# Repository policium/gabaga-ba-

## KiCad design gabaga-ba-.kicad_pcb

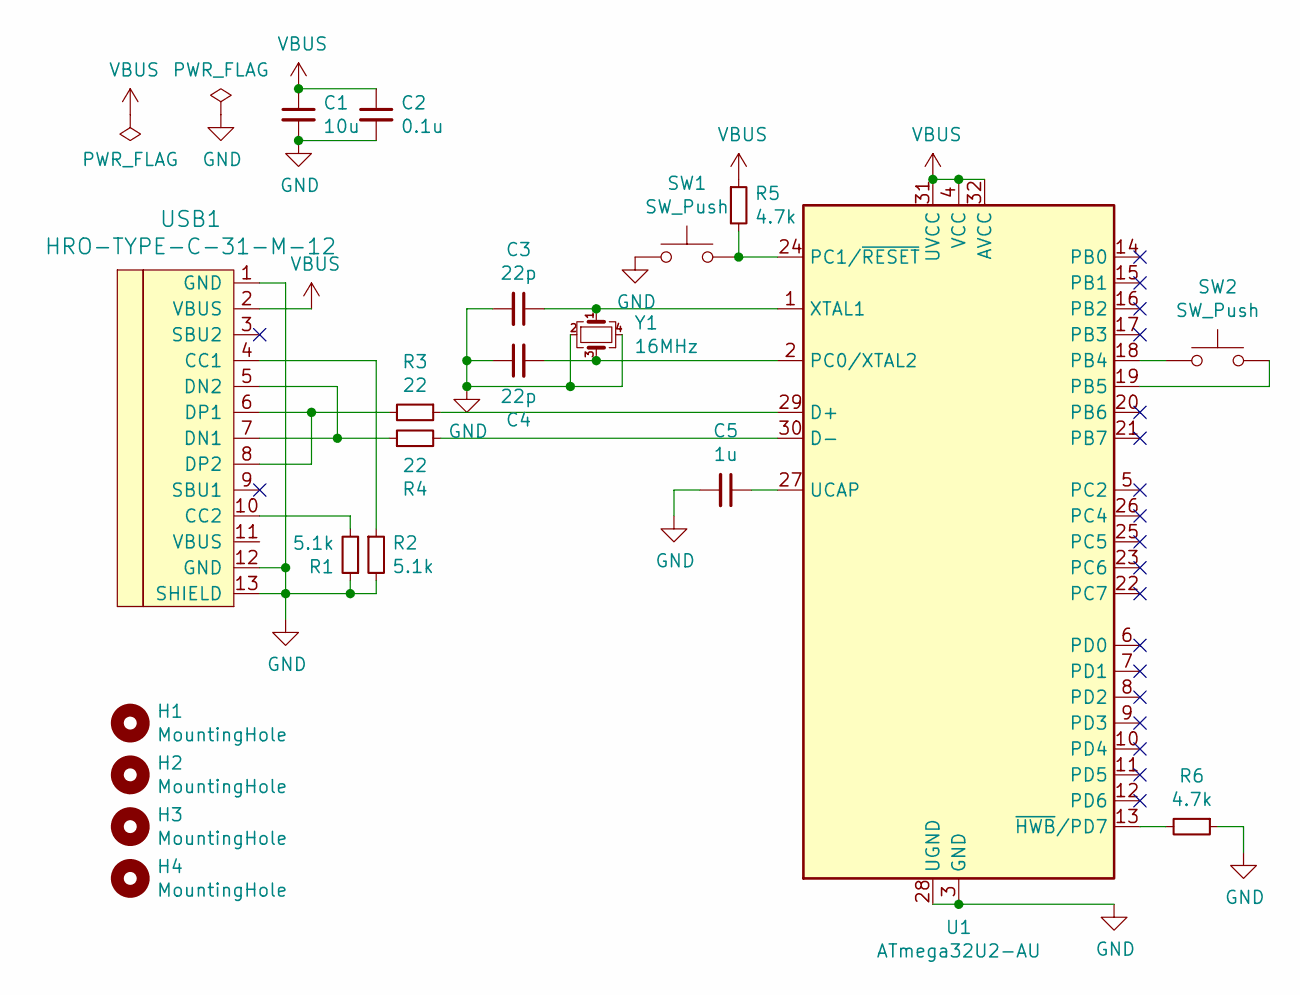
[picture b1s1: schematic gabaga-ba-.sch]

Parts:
C1: 10u; C_0805_2012Metric
C2: 0.1u; C_0805_2012Metric
C3, C4: 22p; C_0805_2012Metric
C5: 1u; C_0805_2012Metric
H1, H2, H3, H4: MountingHole; MountingHole_3.2mm_M3
R1, R2: 5.1k; R_0805_2012Metric
R3, R4: 22; R_0805_2012Metric
R5, R6: 4.7k; R_0805_2012Metric
SW1: SW_Push; SW_SPST_SKQG_WithStem
SW2: SW_Push; kailh_big_series
U1: ATmega32U2-AU; TQFP-32_7x7mm_P0.8mm
USB1: HRO-TYPE-C-31-M-12
Y1: 16MHz; Crystal_SMD_5032-4Pin_5.0x3.2mm

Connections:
GND: C1.2, C2.2, C3.2, C4.1, C5.2, R1.1, R2.2, R6.1, SW1.1, U1.3 (GND), U1.28 (UGND), USB1.1 (GND), USB1.12 (GND), USB1.13 (SHIELD), Y1.2, Y1.4
unnamed: C3.1, U1.1 (XTAL1), Y1.1
unnamed: C4.2, U1.2 (PC0/XTAL2), Y1.3
unnamed: C5.1, U1.27 (UCAP)
unnamed: R1.2, USB1.10 (CC2)
unnamed: R2.1, USB1.4 (CC1)
unnamed: R3.1, U1.29 (D+)
unnamed: R3.2, USB1.6 (DP1), USB1.8 (DP2)
unnamed: R4.1, USB1.5 (DN2), USB1.7 (DN1)
unnamed: R4.2, U1.30 (D-)
unnamed: R5.2, SW1.2, U1.24 (PC1/~RESET)
unnamed: R6.2, U1.13 (~HWB~/PD7)
unnamed: SW2.1, U1.18 (PB4)
unnamed: SW2.2, U1.19 (PB5)
VBUS: C1.1, C2.1, R5.1, U1.4 (VCC), U1.31 (UVCC), U1.32 (AVCC), USB1.2 (VBUS)

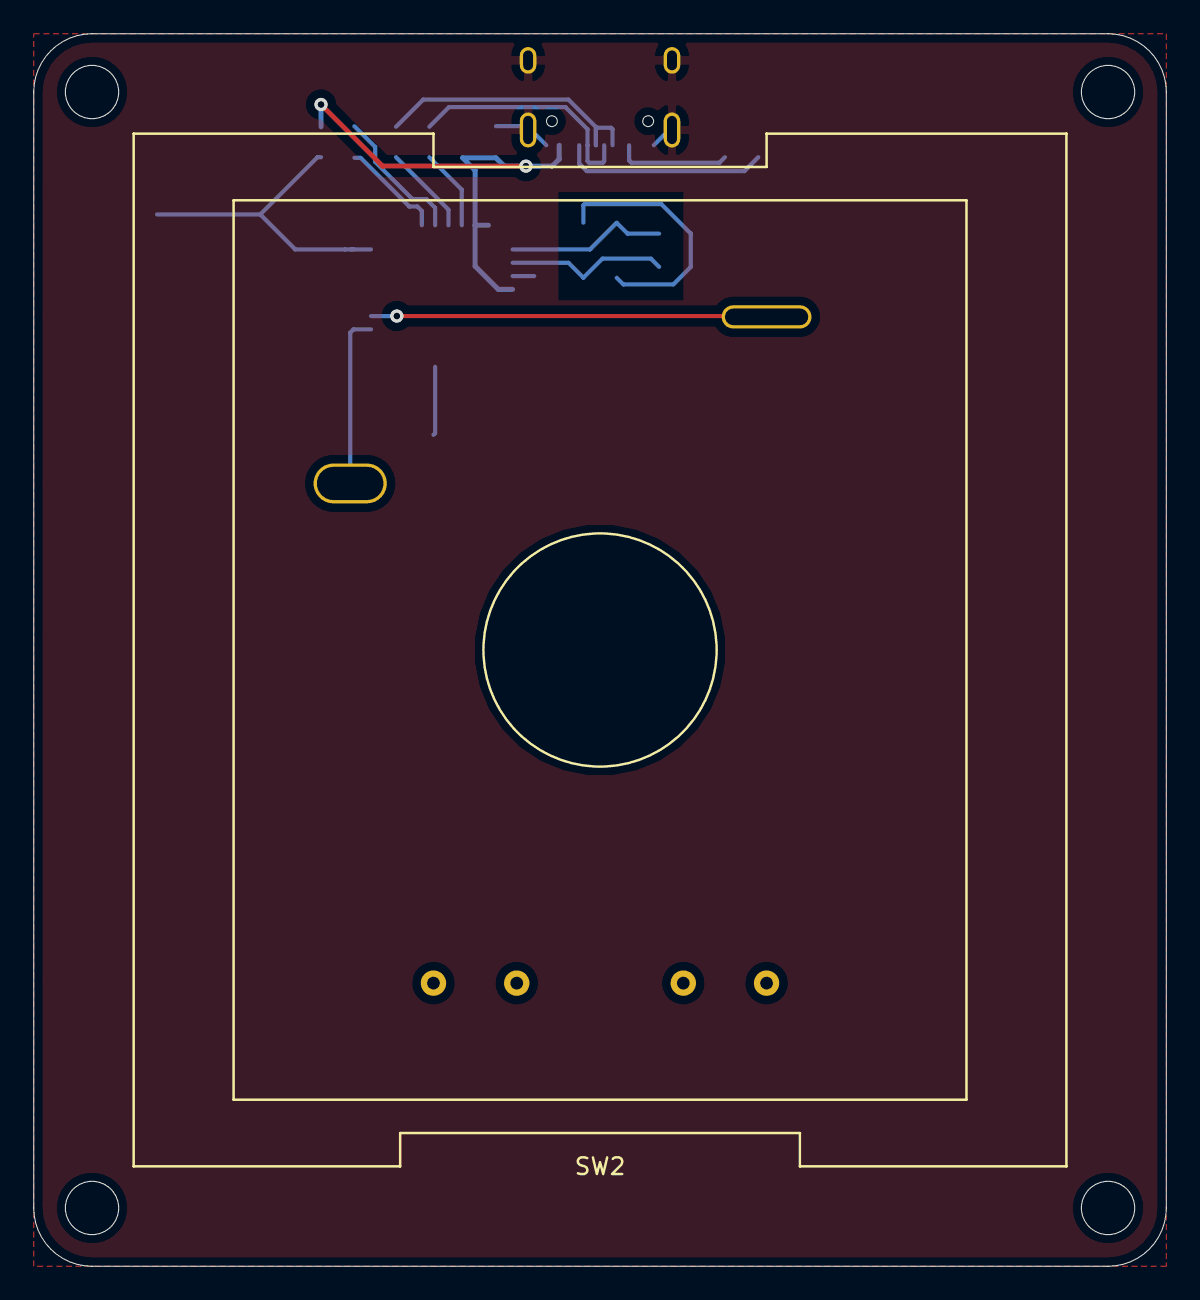
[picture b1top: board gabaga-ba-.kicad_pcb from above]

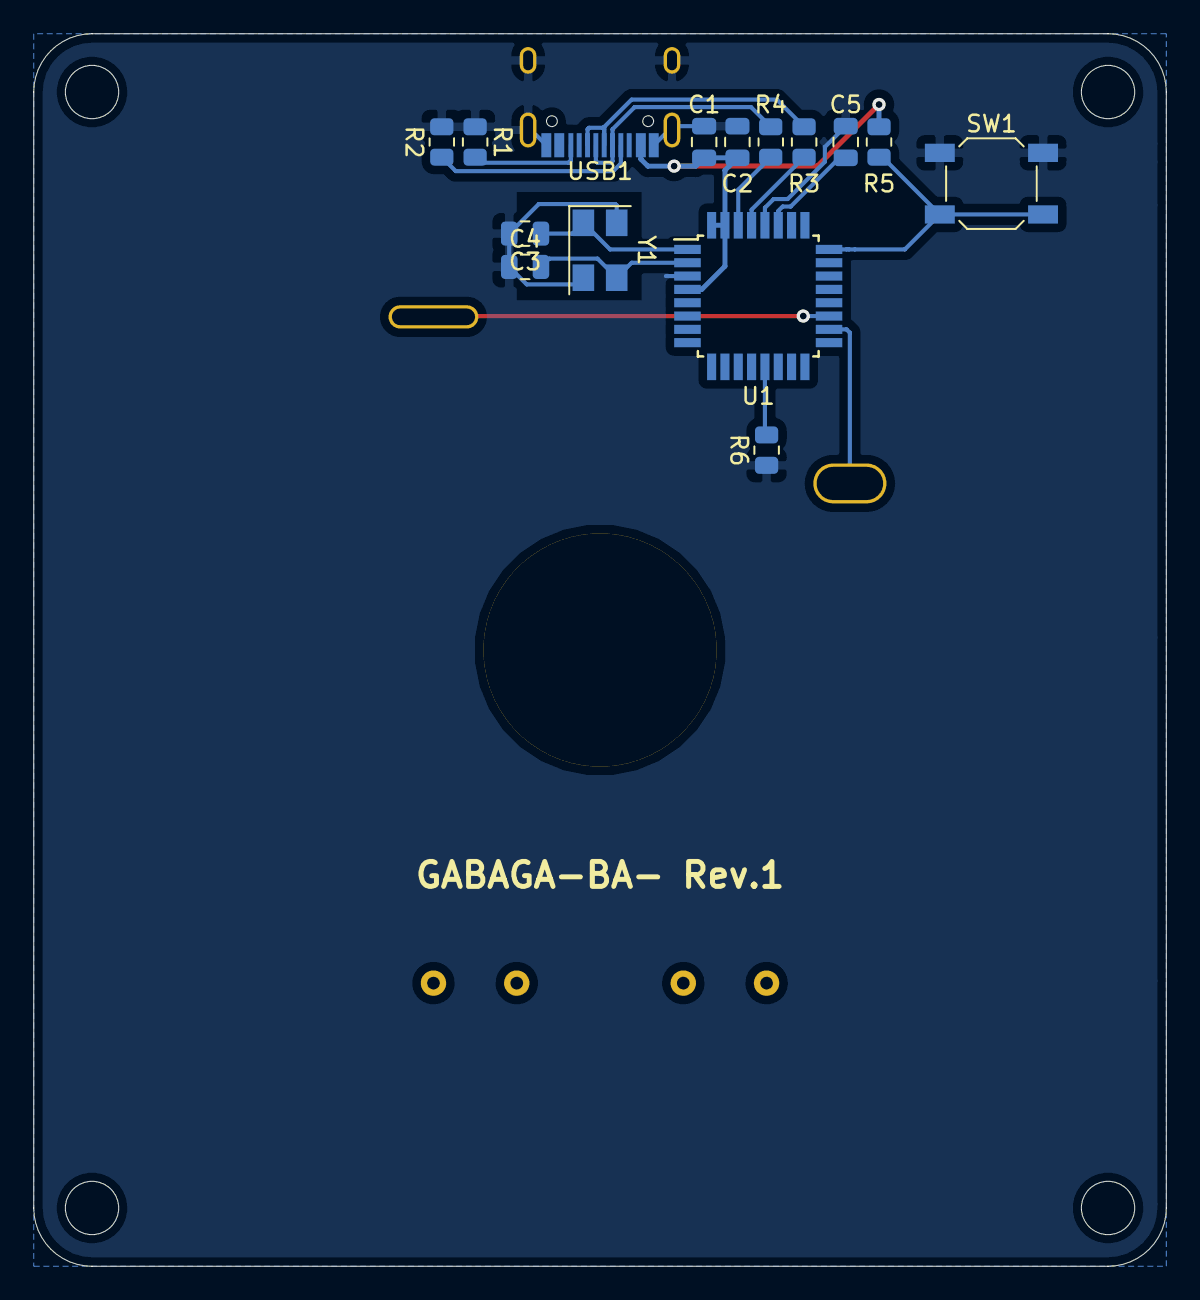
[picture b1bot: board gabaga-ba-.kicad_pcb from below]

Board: 2 copper layers, 68.0 x 74.0 mm, 20 parts (15 on the bottom side), 15 nets.
